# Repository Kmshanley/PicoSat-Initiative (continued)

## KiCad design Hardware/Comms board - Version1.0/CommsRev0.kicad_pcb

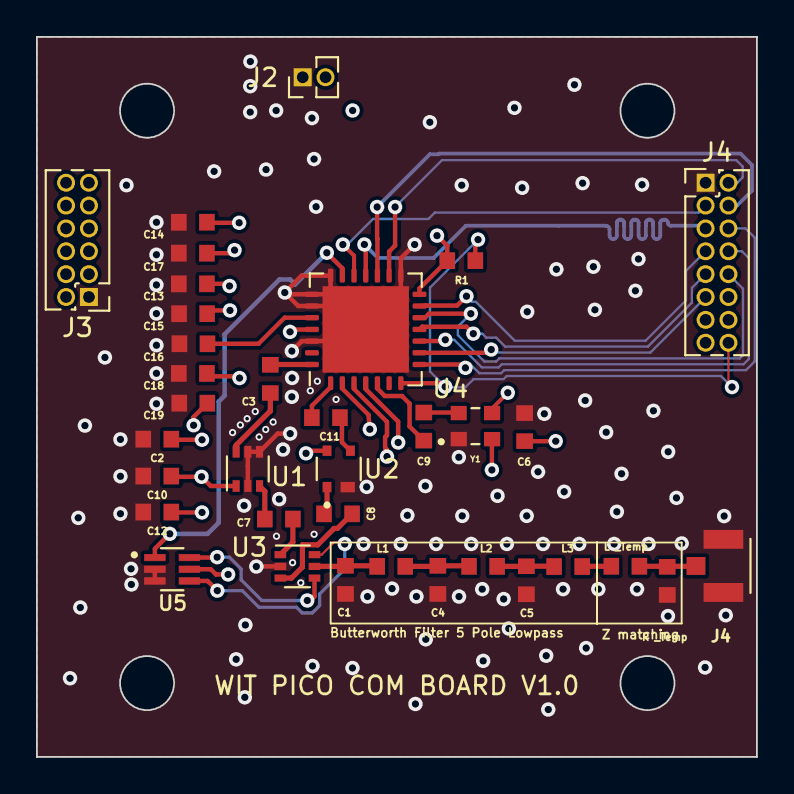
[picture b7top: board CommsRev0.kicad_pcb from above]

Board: 4 copper layers, 40.0 x 40.0 mm, 35 parts (0 on the bottom side), 35 nets.

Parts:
C1, C5: 2.236 pF; RESC1608X55N
C2: 50 pF; RESC1608X55N
C3, C8, C11: 100 pF; RESC1608X55N
C4: 7.234 pF; RESC1608X55N
C6: .1 Uf; RESC1608X55N
C7: 22 nF; RESC1608X55N
C9: 15 pF; RESC1608X55N
C10: 10 nF; RESC1608X55N
C12, C13, C15, C17, C19: 100 nF; RESC1608X55N
C14, C16, C18: 10 uF; RESC1608X55N
J2: Conn_01x02_Pin; PinHeader_1x02_P1.27mm_Vertical
J3: Conn_01x12_Socket; PinHeader_2x06_P1.27mm_Vertical
J4: Conn_01x16_Socket; PinHeader_2x08_P1.27mm_Vertical
J4#2: Conn_Coaxial; TE_1909763-1
L1, L2: 14.632 nH; RESC1608X55N
L3: 3.9 nH; RESC1608X55N
L _Temp: 3.9 nH; RESC1608X55N
R1, R1#2: 4.7k; RESC1608X55N
U1: BGA2801; SOT-363_SC-70-6
U2: BGA420; INFINEON_BFP540
U3: AS179-92LF; SOT-363_SC-70-6
U4: SX1278; QFN-28-1EP_6x6mm_P0.65mm_EP4.8x4.8mm
U5: 74LVC1G19; SOT65P210X110-6N
Y1: ECS-TXO-2520-33-400-AN-TR; OSC_ECS-TXO-2520-33-400-AN-TR

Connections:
+3.3V: C2.2, C6.1, C10.1, C12.1, C14.1, C17.1, C19.1, J2.2, J3.12, J4.12, R1.1, U1.1 (Vcc), U2.4 (VD), U4.14 (VBAT_DIG), U4.25 (VR_PA), U5.5 (VCC), Y1.2 (GND), Y1.3 (OUTPUT)
/Antenna_Control: U4.20 (RXTX/RF_MOD), U5.1 (A)
/DECODER_OUT_1: U3.4 (V1), U5.6 (Y0)
/DECODER_OUT_2: U3.6 (V2), U5.4 (Y1)
/DIO_0: J4.6, U4.8 (DIO0)
/DIO_1: J4.11, U4.9 (DIO1)
/DIO_2: J4.8, U4.10 (DIO2)
/DIO_3: J4.9, U4.11 (DIO3)
/DIO_4: J4.10, U4.12 (DIO4)
/DIO_5: J4.7, U4.13 (DIO5)
/Filter_Input: C1.1, L1.1, U3.5 (J1)
/Filter_Output: L3.2, L _Temp.1
/LNA_INPUT: C8.1, U3.3 (J2)
/LNA_OUTPUT: C11.2, U4.1 (RFI_LF)
/MISO: J4.4, U4.17 (MISO)
/MOSI: J4.5, U4.18 (MOSI)
/NSS: J4.3, U4.19 (NSS)
/PA_Input: C3.1, U4.28 (RFO_LF)
/PA_OUTPUT: C7.2, U3.1 (J3)
/Reset: J4.16, R1.2, U4.7 (~RESET)
/SCK: J4.2, U4.16 (SCK)
/TCXO_OUT: C9.2, U4.5 (XTA)
GND: C1.2, C2.1, C4.2, C5.2, C6.2, C10.2, C12.2, C13.2, C14.2, C15.2, C16.2, C17.2, C18.2, C19.2, J2.1, J3.1, J4.1, J4#2.2 (Ext), J4#2.3 (Ext), R1#2.1, U1.2 (G), U1.4 (G), U1.5 (G), U2.2 (GND), U3.2 (GND), U4.15 (GND), U4.21 (RFI_HF), U4.22 (RFO_HF), U4.23 (GND), U4.26 (GND), U4.29 (GND), U5.2 (GND), U5.3 (~E), Y1.1 (TRI-STATE)
unnamed: C3.2, U1.6
unnamed: C4.1, L1.2, L2.1
unnamed: C5.1, L2.2, L3.1
unnamed: C7.1, U1.3
unnamed: C8.2, U2.1 (IN)
unnamed: C11.1, U2.3 (OUT)
unnamed: C18.1, U4.3 (VBAT_ANA)
unnamed: C16.1, U4.24 (VBAT_RF)
unnamed: C15.1, U4.2 (VR_ANA)
unnamed: C13.1, U4.4 (VR_DIG)
unnamed: C9.1, Y1.4 (VDD)
temp: J4#2.1 (In), L _Temp.2, R1#2.2

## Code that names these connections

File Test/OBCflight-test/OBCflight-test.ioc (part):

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Mcu.Name=STM32H723ZGTx
Mcu.Package=LQFP144
Mcu.UserName=STM32H723ZGTx
PA0.Mode=WakeUp1
PA0.Signal=PWR_WKUP1
PA1.Signal=S_TIM5_CH2
PA10.Mode=Asynchronous
PA10.Signal=USART1_RX
PA11.Mode=Device_Only_FS
PA11.Signal=USB_OTG_HS_DM
PA12.Mode=Device_Only_FS
PA12.Signal=USB_OTG_HS_DP
PA13(JTMS/SWDIO).Mode=JTAG_4_pins
PA13(JTMS/SWDIO).Signal=DEBUG_JTMS-SWDIO
PA14(JTCK/SWCLK).Mode=JTAG_4_pins
PA14(JTCK/SWCLK).Signal=DEBUG_JTCK-SWCLK
PA15(JTDI).Mode=JTAG_4_pins
PA15(JTDI).Signal=DEBUG_JTDI
PA2.Mode=WakeUp2
PA2.Signal=PWR_WKUP2
PA3.Signal=S_TIM5_CH4
PA4.Mode=Slave_12_bits_External_Synchro
PA4.Signal=DCMI_HSYNC
PA5.Mode=MonitoringState
PA5.Signal=PWR_NDSTOP2
PA6.Mode=Slave_12_bits_External_Synchro
PA6.Signal=DCMI_PIXCLK
PA7.Signal=S_TIM3_CH2
PA8.Signal=GPIO_Output
PA9.Mode=Activate_VBUS_FS
PA9.Signal=USB_OTG_HS_VBUS
PB0.Signal=S_TIM3_CH3
PB1.Signal=S_TIM3_CH4
PB10.Mode=I2C
PB10.Signal=I2C2_SCL
PB11.Mode=I2C
PB11.Signal=I2C2_SDA
PB12.Mode=OCTOSPI1_IOL_Port1L
PB12.Signal=OCTOSPIM_P1_IO0
PB13.Mode=OCTOSPI1_IOL_Port1L
PB13.Signal=OCTOSPIM_P1_IO2
PB14.Signal=S_TIM12_CH1
PB15.Signal=S_TIM12_CH2
PB3(JTDO/TRACESWO).Mode=JTAG_4_pins
PB3(JTDO/TRACESWO).Signal=DEBUG_JTDO-SWO
PB4(NJTRST).Signal=S_TIM3_CH1
PB5.Mode=Slave_12_bits_External_Synchro
PB5.Signal=DCMI_D10
PB6.Mode=Asynchronous
PB6.Signal=USART1_TX
PB7.Mode=I2C
PB7.Signal=I2C1_SDA
PB8.Mode=I2C
PB8.Signal=I2C1_SCL
PB9.Signal=GPIO_Output
PC1.Mode=OCTOSPI1_IOH_Port1H
PC1.Signal=OCTOSPIM_P1_IO4
PC10.Mode=Slave_12_bits_External_Synchro
PC10.Signal=DCMI_D8
PC11.Signal=GPIO_Output
PC12.Mode=Slave_12_bits_External_Synchro
PC12.Signal=DCMI_D9
PC13.Mode=WakeUp4
PC13.Signal=PWR_WKUP4
PC14-OSC32_IN.Mode=LSE-External-Oscillator
PC14-OSC32_IN.Signal=RCC_OSC32_IN
PC15-OSC32_OUT.Mode=LSE-External-Oscillator
PC15-OSC32_OUT.Signal=RCC_OSC32_OUT
PC2_C.Mode=MonitoringState
PC2_C.Signal=PWR_CSTOP
PC3_C.Mode=MonitoringState
PC3_C.Signal=PWR_CSLEEP
PC5.Mode=OCTOSPI1_Port1_DQS
PC5.Signal=OCTOSPIM_P1_DQS
PC6.Mode=Slave_12_bits_External_Synchro
PC6.Signal=DCMI_D0
PC7.Mode=Slave_12_bits_External_Synchro
PC7.Signal=DCMI_D1
PC8.Mode=Slave_12_bits_External_Synchro
PC8.Signal=DCMI_D2
PC9.Mode=Slave_12_bits_External_Synchro
PC9.Signal=DCMI_D3
PD0.Signal=GPIO_Input
PD1.Signal=GPIO_Output
PD10.Signal=GPIO_Output
PD11.Signal=GPIO_Output
PD12.Signal=S_TIM4_CH1
PD13.Signal=S_TIM4_CH2
PD14.Signal=S_TIM4_CH3
PD15.Signal=S_TIM4_CH4
PD2.Mode=Slave_12_bits_External_Synchro
PD2.Signal=DCMI_D11
PD3.Mode=Slave_12_bits_External_Synchro
PD3.Signal=DCMI_D5
PD4.Signal=GPIO_Output
PD5.Mode=Asynchronous
PD5.Signal=USART2_TX
PD6.Mode=Asynchronous
PD6.Signal=USART2_RX
PD7.Signal=GPIO_Output
PD8.Signal=GPIO_Output
PD9.Signal=GPIO_Output
PE0.Signal=GPIO_Output
PE1.Signal=GPIO_Output
PE10.Mode=OCTOSPI1_IOH_Port1H
PE10.Signal=OCTOSPIM_P1_IO7
PE11.Mode=NSS_Signal_Hard_Output
PE11.Signal=SPI4_NSS
PE13.Mode=Full_Duplex_Master
PE13.Signal=SPI4_MISO
PE14.Mode=Full_Duplex_Master
PE14.Signal=SPI4_MOSI
PE2.Mode=Full_Duplex_Master
PE2.Signal=SPI4_SCK
PE4.Mode=Slave_12_bits_External_Synchro
PE4.Signal=DCMI_D4
PE5.Mode=Slave_12_bits_External_Synchro
PE5.Signal=DCMI_D6
PE6.Mode=Slave_12_bits_External_Synchro
PE6.Signal=DCMI_D7
PE8.Mode=OCTOSPI1_IOH_Port1H
PE8.Signal=OCTOSPIM_P1_IO5
PE9.Mode=OCTOSPI1_IOH_Port1H
PE9.Signal=OCTOSPIM_P1_IO6
PF0.Mode=OCTOSPI2_IOL_Port2L
PF0.Signal=OCTOSPIM_P2_IO0
PF1.Mode=OCTOSPI2_IOL_Port2L
PF1.Signal=OCTOSPIM_P2_IO1
PF10.Mode=O1_P1_CLK
PF10.Signal=OCTOSPIM_P1_CLK
PF11.Mode=Full_Duplex_Master
PF11.Signal=SPI5_MOSI
PF14.Mode=I2C
PF14.Signal=I2C4_SCL
PF15.Mode=I2C
PF15.Signal=I2C4_SDA
PF2.Mode=OCTOSPI2_IOL_Port2L
PF2.Signal=OCTOSPIM_P2_IO2
PF3.Mode=OCTOSPI2_IOL_Port2L
PF3.Signal=OCTOSPIM_P2_IO3
PF4.Mode=O2_P2_CLK
PF4.Signal=OCTOSPIM_P2_CLK
PF5.Signal=GPIO_Output
PF6.Mode=OCTOSPI1_IOL_Port1L
PF6.Signal=OCTOSPIM_P1_IO3
PF7.Mode=Full_Duplex_Master
PF7.Signal=SPI5_SCK
PF8.Mode=Full_Duplex_Master
PF8.Signal=SPI5_MISO
PF9.Mode=OCTOSPI1_IOL_Port1L
PF9.Signal=OCTOSPIM_P1_IO1
PG0.Mode=OCTOSPI2_IOH_Port2H
PG0.Signal=OCTOSPIM_P2_IO4
PG1.Mode=OCTOSPI2_IOH_Port2H
PG1.Signal=OCTOSPIM_P2_IO5
PG10.Mode=OCTOSPI2_IOH_Port2H
PG10.Signal=OCTOSPIM_P2_IO6
PG11.Mode=OCTOSPI2_IOH_Port2H
PG11.Signal=OCTOSPIM_P2_IO7
PG12.Mode=OCTOSPI2_Port2_NCS
PG12.Signal=OCTOSPIM_P2_NCS
PG13.Signal=GPIO_Output
PG14.Signal=GPIO_Output
PG15.Signal=GPIO_Output
PG2.Signal=GPIO_Output
PG3.Signal=GPIO_Output
PG4.Signal=GPIO_Output
PG5.GPIOParameters=PinState,GPIO_PuPd
PG5.GPIO_PuPd=GPIO_PULLUP
PG5.PinState=GPIO_PIN_SET
PG5.Signal=GPIO_Output
PG6.Mode=OCTOSPI1_Port1_NCS
PG6.Signal=OCTOSPIM_P1_NCS
PG7.Signal=GPIO_Output
PG8.Signal=GPIO_Output
PG9.Mode=Slave_12_bits_External_Synchro
PG9.Signal=DCMI_VSYNC
PH0-OSC_IN.Mode=HSE-External-Oscillator
PH0-OSC_IN.Signal=RCC_OSC_IN
PH1-OSC_OUT.Mode=HSE-External-Oscillator
PH1-OSC_OUT.Signal=RCC_OSC_OUT
RCC.HSE_VALUE=48000000
RCC.SYSCLKFreq_VALUE=550000000
RCC.SYSCLKSource=RCC_SYSCLKSOURCE_PLLCLK
board=custom

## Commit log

2023-01-19 Add OV5640 test program
    This program will use DCMI to grab a image from a attached OV5640 and place it into internal memory.
2023-03-13 New test project
    This project will test I2C comms with the INA219 and MAX17048
2023-05-22 DevBoard test project Initial commit
2023-06-27 Initial Basic functions
    Implement basic functions of NAND flash chip. Includes read, write, erase, and manipulate status registers.
2023-06-28 Add configuration for 2nd octospi
    Auto generated configuration for second Octospi that is connected to NAND flash.
2023-07-17 Updated readme
    Added a basic readme.
2023-07-17 Create readme for test programs
    This readme will detail what each program does and what it's purpose is for easy reference.
2023-07-22 Update gitignore
2023-07-22 Update gitignore
    Update gitignore
2023-07-22 Update CubeIDE Version
2023-07-22 Remove New Ignored Files
2023-07-22 clock changes
    fixed clock to use hsi again
2023-08-01 tmp117
    temp sensor commit
2023-08-15 Gyro and Accel get functions
    From looking at datasheets and existing sensor code, I believe these functions should be able to get the values for the accelerometer and gyroscope for the ICM20948 device
2023-09-05 Cleaned up some read functions and variable names
2023-09-05 Added ManuID read to INA236
    saw that this function was in the header but not in the c file, so decided to add it since it was mainly just copy pasting and changing a couple of names
2023-09-05 Sensitivity read and write functions
    Set up functions to both set and read sensitivity for both accelerometer and gyroscope. Also modified pre-existing functions, replacing placeholder variables (ACCEL_SENSITIVITY or GYRO_SENSITIVITY) w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
2023-09-06 Included ICM20948 files in main.c, added various tests to check for errors
    Currently, my functions are not working, still working on how to figure it out. Let me know if you check this version and see any obvious errors, as I'm not really sure how i2c works.
2023-09-12 Troubleshooting in progress
    Receiving values of zero from all my read functions. Not sure why, still working on it.
2023-10-27 Initial Commit for OBC-flight
    Groundwork for a OCB-flight test program.
2023-11-30 Overview for readme
    Provide a brief overview of the project and hardware for the landing page.
2023-12-01 Documentation for Persistent Storage
    Document and diagram the satellites persistent storage system.
2023-12-01 Documentation for camera system
2024-07-17 Add Hardware
    Add KiCad PCB designs to version control
